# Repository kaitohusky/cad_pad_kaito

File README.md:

# 3×5 CAD Shortcut Keyboard

A compact 15-key USB shortcut keyboard designed to trigger shortcuts in CAD software.  
Built around a **Seeed XIAO RP2040 (DIP version)** using a **3×5 diode-protected key matrix** (anti-ghosting).

This repo contains the full hardware + firmware stack: schematic, PCB layout, assembly references, and firmware that sends USB key events to the computer.

---

## Repository Structure

- **PCB/**: KiCad project files (schematic + PCB layout)
- **Firmware/**: firmware source code
- **docs/**: screenshots used in this README

---

## Hardware Overview

### Purpose
CAD workflows rely heavily on shortcuts (sketch tools, constraints, navigation, etc.). A full keyboard works, but it increases hand travel and breaks focus. This small keyboard provides **15 dedicated keys** mapped to the most-used CAD actions.

### Main Characteristics
- 15 keys total
- 3 rows × 5 columns matrix
- 1 diode per key (ghosting prevention)
- USB connection via XIAO RP2040
- Optional per-key RGB backlight (SK6812 addressable LEDs)
- PCB constrained to **≤ 100 mm × 100 mm**

---

## Schematic

---

## Key Matrix

The keys are wired as a matrix to reduce GPIO usage:
- Rows configured as **outputs**
- Columns configured as **inputs with pull-ups**
- Each key uses **one series diode** to prevent ghosting during matrix scanning

Electrical structure per key:

~~~text
ROW → diode → switch → COLUMN
~~~

Diode orientation rule used in this design:
- **Diode stripe faces the row net** (cathode on the row side)

This allows columns to be pulled low when a row is driven low and a switch is pressed.

---

## GPIO Pin Mapping (Seeed XIAO RP2040)

### Rows (outputs)

| Row | GPIO |
|-----|------|
| R0  | GPIO26 |
| R1  | GPIO27 |
| R2  | GPIO28 |

### Columns (inputs with pull-ups)

| Column | GPIO |
|--------|------|
| C0     | GPIO29 |
| C1     | GPIO0  |
| C2     | GPIO1  |
| C3     | GPIO2  |
| C4     | GPIO4  |

### Optional RGB LED chain (SK6812)
- LEDs powered from **USB 5V (VBUS)** and **GND**
- Data from a free GPIO (example: **GPIO3**) into **LED1 DIN**
- Daisy-chain **DOUT → DIN** across all 15 LEDs

---

## PCB Layout

### Mechanical / Placement
- Key spacing: **19.05 mm** center-to-center (standard MX spacing)
- Board outline designed to fit within the **100×100 mm** maximum
- Switch footprint: `SW_Cherry_MX_1.00u_PCB`
- LEDs placed near each switch footprint (outside switch courtyard)
- Diodes placed close to switches (can be bottom-side to free space and simplify routing)

---

## Assembly

### Assembly Steps
1. Solder the diodes (verify stripe orientation toward row nets)
2. Solder the SK6812 LEDs (optional; verify DIN/DOUT direction)
3. Solder the Seeed XIAO RP2040 module
4. Solder the MX switches
5. Flash the firmware
6. Connect over USB and validate key presses and shortcuts

---

## Firmware

Firmware location:

~~~text
Firmware/main.py
~~~

This project uses **CircuitPython** with a **KMK-style** approach (single `main.py`).  
The firmware scans the 3×5 matrix and sends USB keyboard events to the host computer. Keys are currently mapped to **placeholder shortcuts** that can be replaced with the exact shortcuts used by your CAD tool.

---

## BOM (Bill of Materials)

### Core (required)

| Item | Qty | Notes |
|------|-----|------|
| Seeed Studio XIAO RP2040 (DIP) | 1 | Main controller, USB-C |
| Custom PCB (≤100×100 mm) | 1 | From this repo KiCad files |
| Cherry MX compatible switches | 15 | Any MX-style (linear/tactile/clicky) |
| Keycaps (1u) | 15 | Any MX keycap set |
| Signal diodes | 15 | **1 per key** (ex: 1N4148 THT or 1N4148W SMD) |
| USB cable (USB-C) | 1 | For power + data |

### Optional (RGB backlight)

| Item | Qty | Notes |
|------|-----|------|
| SK6812 / NeoPixel-compatible addressable LEDs | 15 | Per-key RGB (choose SMD package that matches footprint) |
| Decoupling capacitor for LED power rail | 1–2 | Typical: 100 µF electrolytic + 0.1 µF ceramic near LED rail |
| Series resistor on LED data line | 1 | Typical: 330–470 Ω between GPIO and first LED DIN |

### Optional (mechanical)

| Item | Qty | Notes |
|------|-----|------|
| Case / plate (3D printed or laser cut) | 1 | If you want a rigid enclosure |
| Rubber feet | 4 | Desk grip |
| M2 / M3 screws + standoffs | 4–8 | Depends on case design |

---

## Intended Shortcut Usage (Example)

Typical categories to map:
- Sketch tools (line, rectangle, circle)
- Constraints (coincident, parallel, perpendicular)
- Navigation (pan, zoom, rotate, view presets)
- Editing (copy, paste, undo, redo)
- Utilities (measure, save)

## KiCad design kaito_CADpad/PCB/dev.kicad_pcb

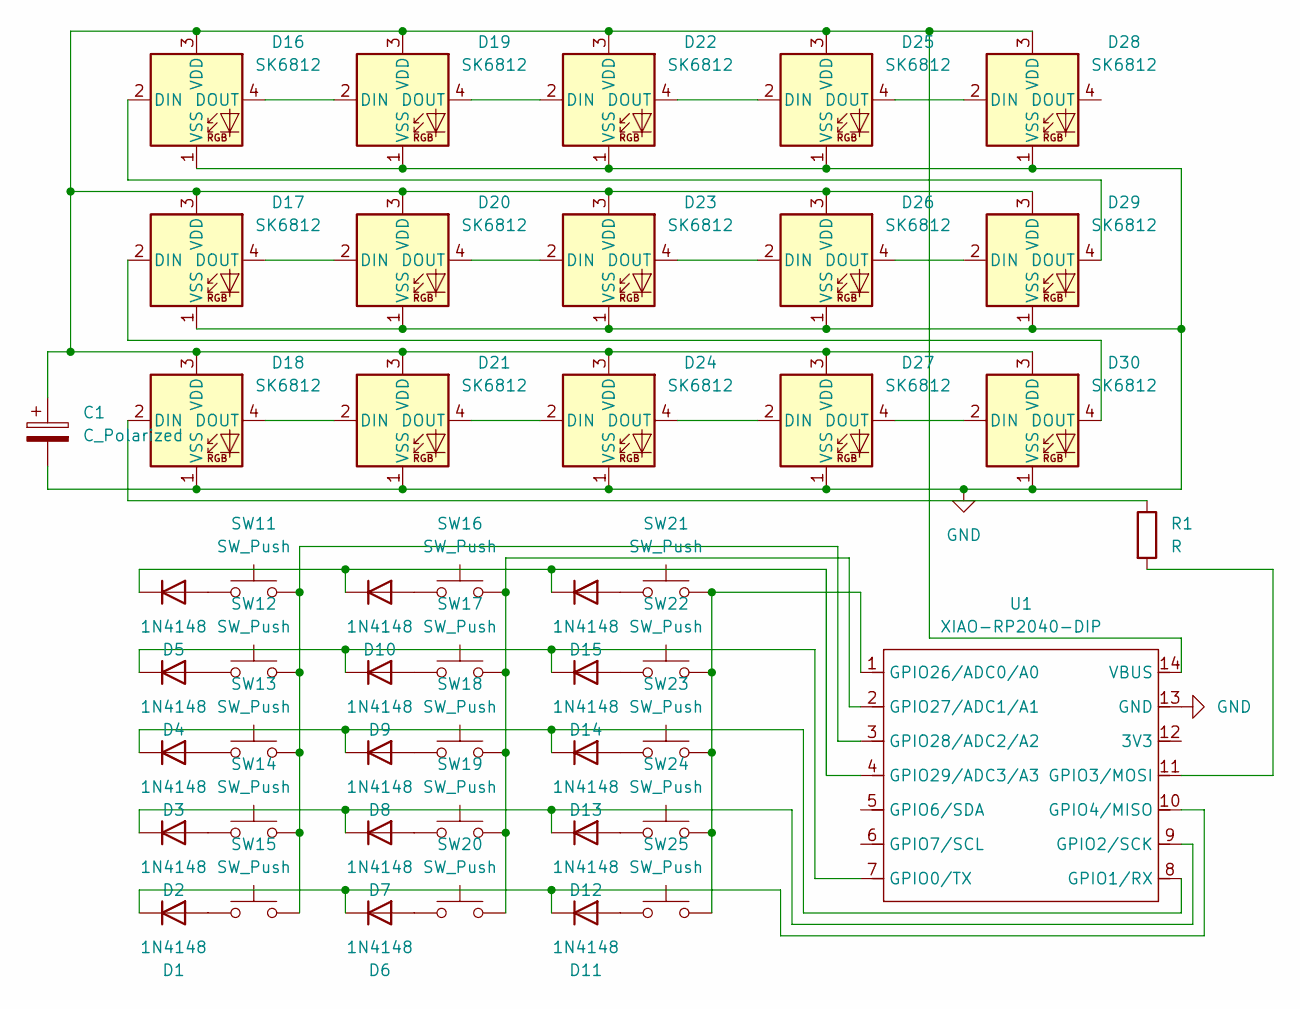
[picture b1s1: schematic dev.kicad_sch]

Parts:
C1: C_Polarized; CP_Radial_D6.3mm_P2.50mm
D1, D2, D3, D4, D5, D6, D7, D8, D9, D10, D11, D12, D13, D14, D15: 1N4148; D_DO-35_SOD27_P7.62mm_Horizontal
D16, D17, D18, D19, D20, D21, D22, D23, D24, D25, D26, D27, D28, D29, D30: SK6812; LED_SK6812_PLCC4_5.0x5.0mm_P3.2mm
R1: R; R_Axial_DIN0204_L3.6mm_D1.6mm_P7.62mm_Horizontal
SW11, SW12, SW13, SW14, SW15, SW16, SW17, SW18, SW19, SW20, SW21, SW22, SW23, SW24, SW25: SW_Push; SW_Cherry_MX_1.00u_PCB
U1: XIAO-RP2040-DIP

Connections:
GND: C1.2, D16.1 (VSS), D17.1 (VSS), D18.1 (VSS), D19.1 (VSS), D20.1 (VSS), D21.1 (VSS), D22.1 (VSS), D23.1 (VSS), D24.1 (VSS), D25.1 (VSS), D26.1 (VSS), D27.1 (VSS), D28.1 (VSS), D29.1 (VSS), D30.1 (VSS), U1.13 (GND)
unnamed: D1.2 (A), SW15.1
unnamed: D1.1 (K), D6.1 (K), D11.1 (K), U1.10 (GPIO4/MISO)
unnamed: D2.2 (A), SW14.1
unnamed: D3.2 (A), SW13.1
unnamed: D4.2 (A), SW12.1
unnamed: D5.2 (A), SW11.1
unnamed: D6.2 (A), SW20.1
unnamed: D7.2 (A), SW19.1
unnamed: D8.2 (A), SW18.1
unnamed: D9.2 (A), SW17.1
unnamed: D10.2 (A), SW16.1
unnamed: D5.1 (K), D10.1 (K), D15.1 (K), U1.4 (GPIO29/ADC3/A3)
unnamed: D11.2 (A), SW25.1
unnamed: D12.2 (A), SW24.1
unnamed: D2.1 (K), D7.1 (K), D12.1 (K), U1.9 (GPIO2/SCK)
unnamed: D13.2 (A), SW23.1
unnamed: D3.1 (K), D8.1 (K), D13.1 (K), U1.8 (GPIO1/RX)
unnamed: D14.2 (A), SW22.1
unnamed: D4.1 (K), D9.1 (K), D14.1 (K), U1.7 (GPIO0/TX)
unnamed: D15.2 (A), SW21.1
unnamed: D16.2 (DIN), D29.4 (DOUT)
unnamed: D16.4 (DOUT), D19.2 (DIN)
unnamed: C1.1, D16.3 (VDD), D17.3 (VDD), D18.3 (VDD), D19.3 (VDD), D20.3 (VDD), D21.3 (VDD), D22.3 (VDD), D23.3 (VDD), D24.3 (VDD), D25.3 (VDD), D26.3 (VDD), D27.3 (VDD), D28.3 (VDD), D29.3 (VDD), D30.3 (VDD), U1.14 (VBUS)
unnamed: D17.2 (DIN), D30.4 (DOUT)
unnamed: D17.4 (DOUT), D20.2 (DIN)
unnamed: D18.2 (DIN), R1.1
unnamed: D18.4 (DOUT), D21.2 (DIN)
unnamed: D19.4 (DOUT), D22.2 (DIN)
unnamed: D20.4 (DOUT), D23.2 (DIN)
unnamed: D21.4 (DOUT), D24.2 (DIN)
unnamed: D22.4 (DOUT), D25.2 (DIN)
unnamed: D23.4 (DOUT), D26.2 (DIN)
unnamed: D24.4 (DOUT), D27.2 (DIN)
unnamed: D25.4 (DOUT), D28.2 (DIN)
unnamed: D26.4 (DOUT), D29.2 (DIN)
unnamed: D27.4 (DOUT), D30.2 (DIN)
unnamed: R1.2, U1.11 (GPIO3/MOSI)
unnamed: SW21.2, SW22.2, SW23.2, SW24.2, SW25.2, U1.1 (GPIO26/ADC0/A0)
unnamed: SW16.2, SW17.2, SW18.2, SW19.2, SW20.2, U1.2 (GPIO27/ADC1/A1)
unnamed: SW11.2, SW12.2, SW13.2, SW14.2, SW15.2, U1.3 (GPIO28/ADC2/A2)

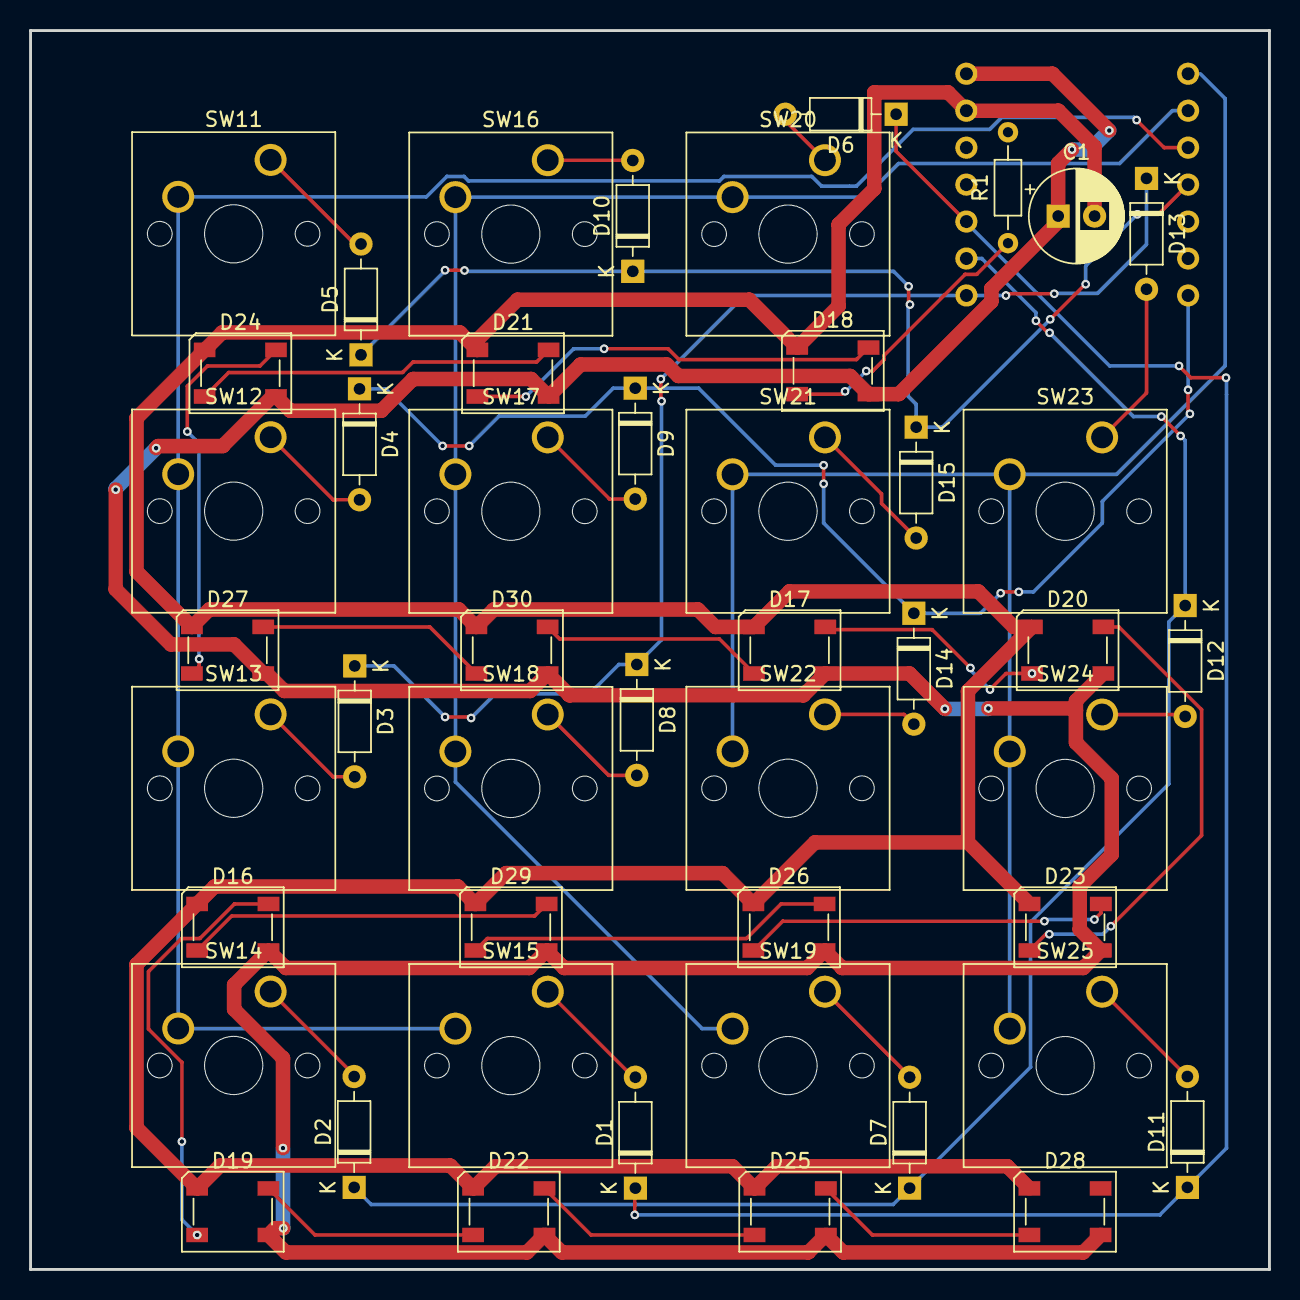
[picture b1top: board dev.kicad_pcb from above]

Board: 2 copper layers, 85.2 x 85.2 mm, 48 parts (1 on the bottom side), 41 nets.
